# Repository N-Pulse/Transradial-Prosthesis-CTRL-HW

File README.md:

# Transradial Prosthesis Control Board

This work is licensed under a Creative Commons Attribution 4.0 International License

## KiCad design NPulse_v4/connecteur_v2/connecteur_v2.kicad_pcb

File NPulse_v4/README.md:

# Transradial Prosthesis Control Board

This work is licensed under a <a rel="license" href="https://creativecommons.org/licenses/by/4.0/">Creative Commons Attribution 4.0 International License</a>.

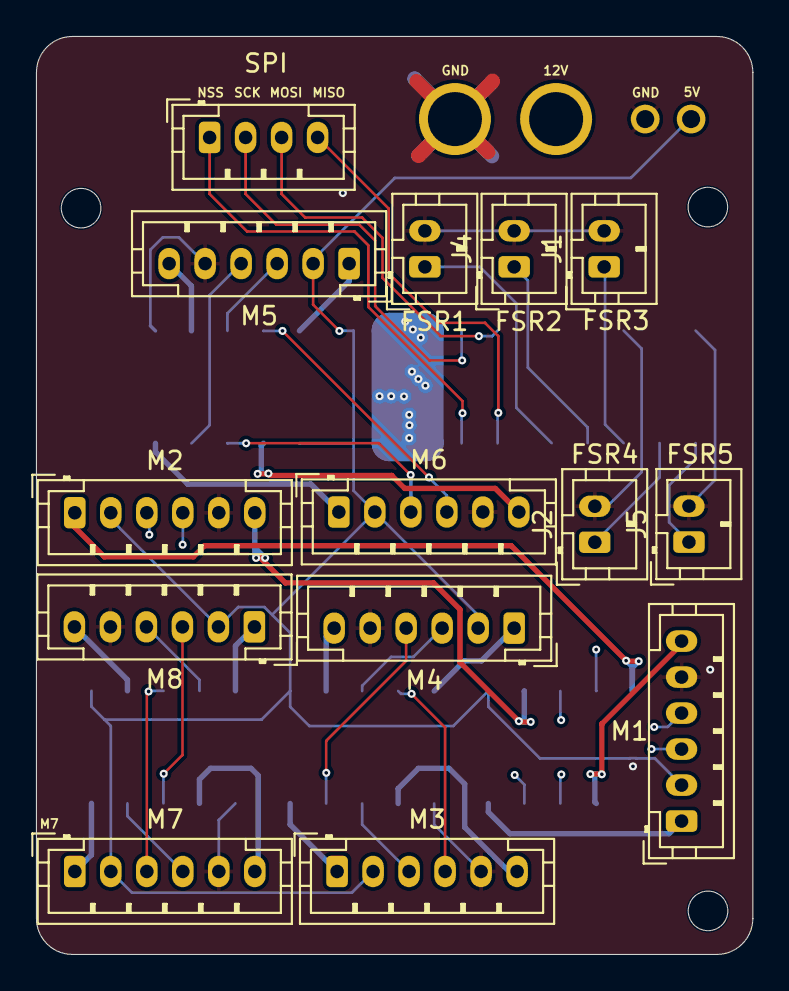
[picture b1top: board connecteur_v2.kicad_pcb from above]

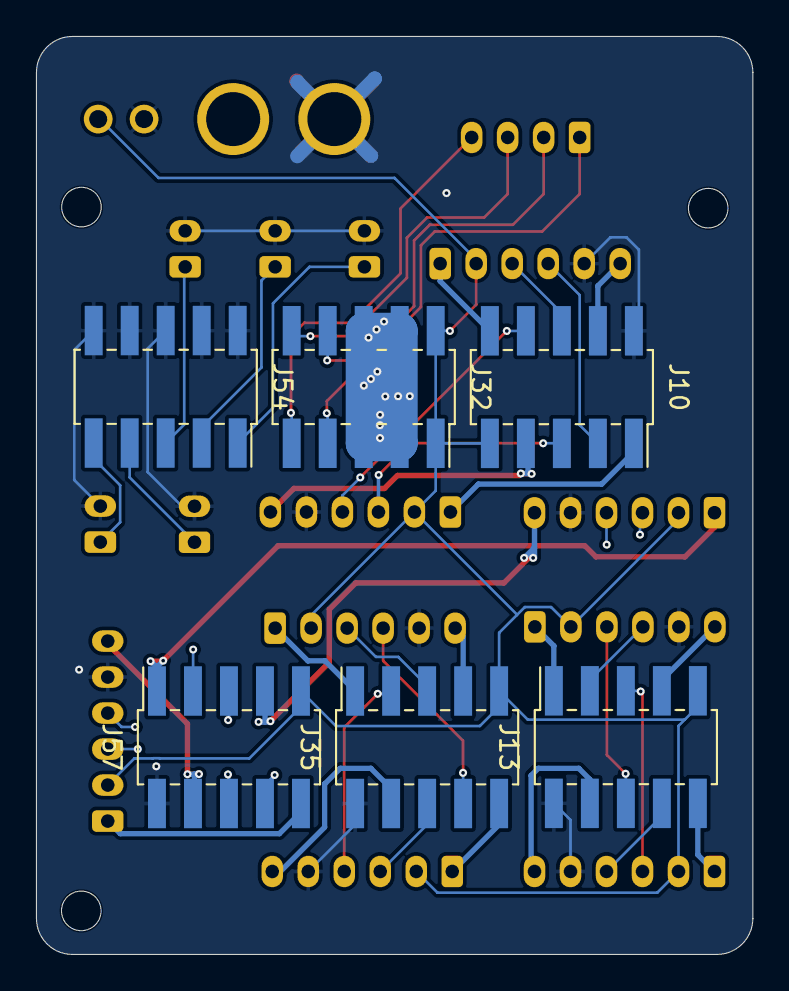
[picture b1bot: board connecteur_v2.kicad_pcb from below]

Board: 4 copper layers, 39.8 x 51.0 mm, 26 parts (6 on the bottom side), 44 nets.

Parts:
H1, H2, H3: MountingHole; MountingHole_2.2mm_M2
J1, J2, J3, J4, J5: Conn_01x02_Socket; JST_PH_B2B-PH-K_1x02_P2.00mm_Vertical
J6: Conn_01x04_Socket; JST_PH_B4B-PH-K_1x04_P2.00mm_Vertical
J10, J13, J32, J35, J54, J57: Conn_02x05_Odd_Even; PinSocket_2x05_P2.00mm_Vertical_SMD
J23, J27, J45: Conn_01x01; SolderWire-0.1sqmm_1x01_D0.4mm_OD1mm
M1, M2, M3, M4, M5, M6, M7, M8: Conn_01x06_Socket; JST_PH_B6B-PH-K_1x06_P2.00mm_Vertical

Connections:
+5V: J10.9, J13.9, J23.1, J32.1, J32.2, J35.9, J57.9, M1.2, M2.2, M3.2, M4.2, M5.2, M6.2, M7.2, M8.2
/+12V: J27.1, J32.3, J32.4, J32.5, J32.6
ENC1_S1: J57.5, M1.4
ENC1_S2: J57.6, M1.3
ENC2_S1: J57.8, M2.4
ENC2_S2: J57.3, M2.3
ENC3_S1: J35.3, M3.4
ENC3_S2: J35.6, M3.3
ENC4_S1: J35.8, M4.4
ENC4_S2: J35.5, M4.3
ENC5_S1: J10.3, M5.4
ENC5_S2: J10.6, M5.3
ENC6_S1: J10.8, M6.4
ENC6_S2: J10.5, M6.3
ENC7_S1: J13.8, M7.4
ENC7_S2: J13.5, M7.3
ENC8_S1: J13.3, M8.4
ENC8_S2: J13.6, M8.3
FSR1: J3.1, J54.1
FSR2: J4.1, J54.3
FSR3: J1.1, J54.5
FSR4: J2.1, J54.7
FSR5: J5.1, J54.9
GND: J1.2, J2.2, J3.2, J4.2, J5.2, J10.2, J13.2, J35.2, J45.1, J54.2, J54.4, J54.6, J54.8, J54.10, J57.2, M1.5, M2.5, M3.5, M4.5, M5.5, M6.5, M7.5, M8.5
M1_1: J57.4, M1.6
M1_2: J57.10, M1.1
M2_1: J57.7, M2.6
M2_2: J57.1, M2.1
M3_1: J35.4, M3.6
M3_2: J35.10, M3.1
M4_1: J35.7, M4.6
M4_2: J35.1, M4.1
M5_1: J10.4, M5.6
M5_2: J10.10, M5.1
M6_1: J10.7, M6.6
M6_2: J10.1, M6.1
M7_1: J13.4, M7.6
M7_2: J13.10, M7.1
M8_1: J13.7, M8.6
M8_2: J13.1, M8.1
MISO: J6.4, J32.9
MOSI: J6.3, J32.10
NSS: J6.1, J32.7
SCK: J6.2, J32.8

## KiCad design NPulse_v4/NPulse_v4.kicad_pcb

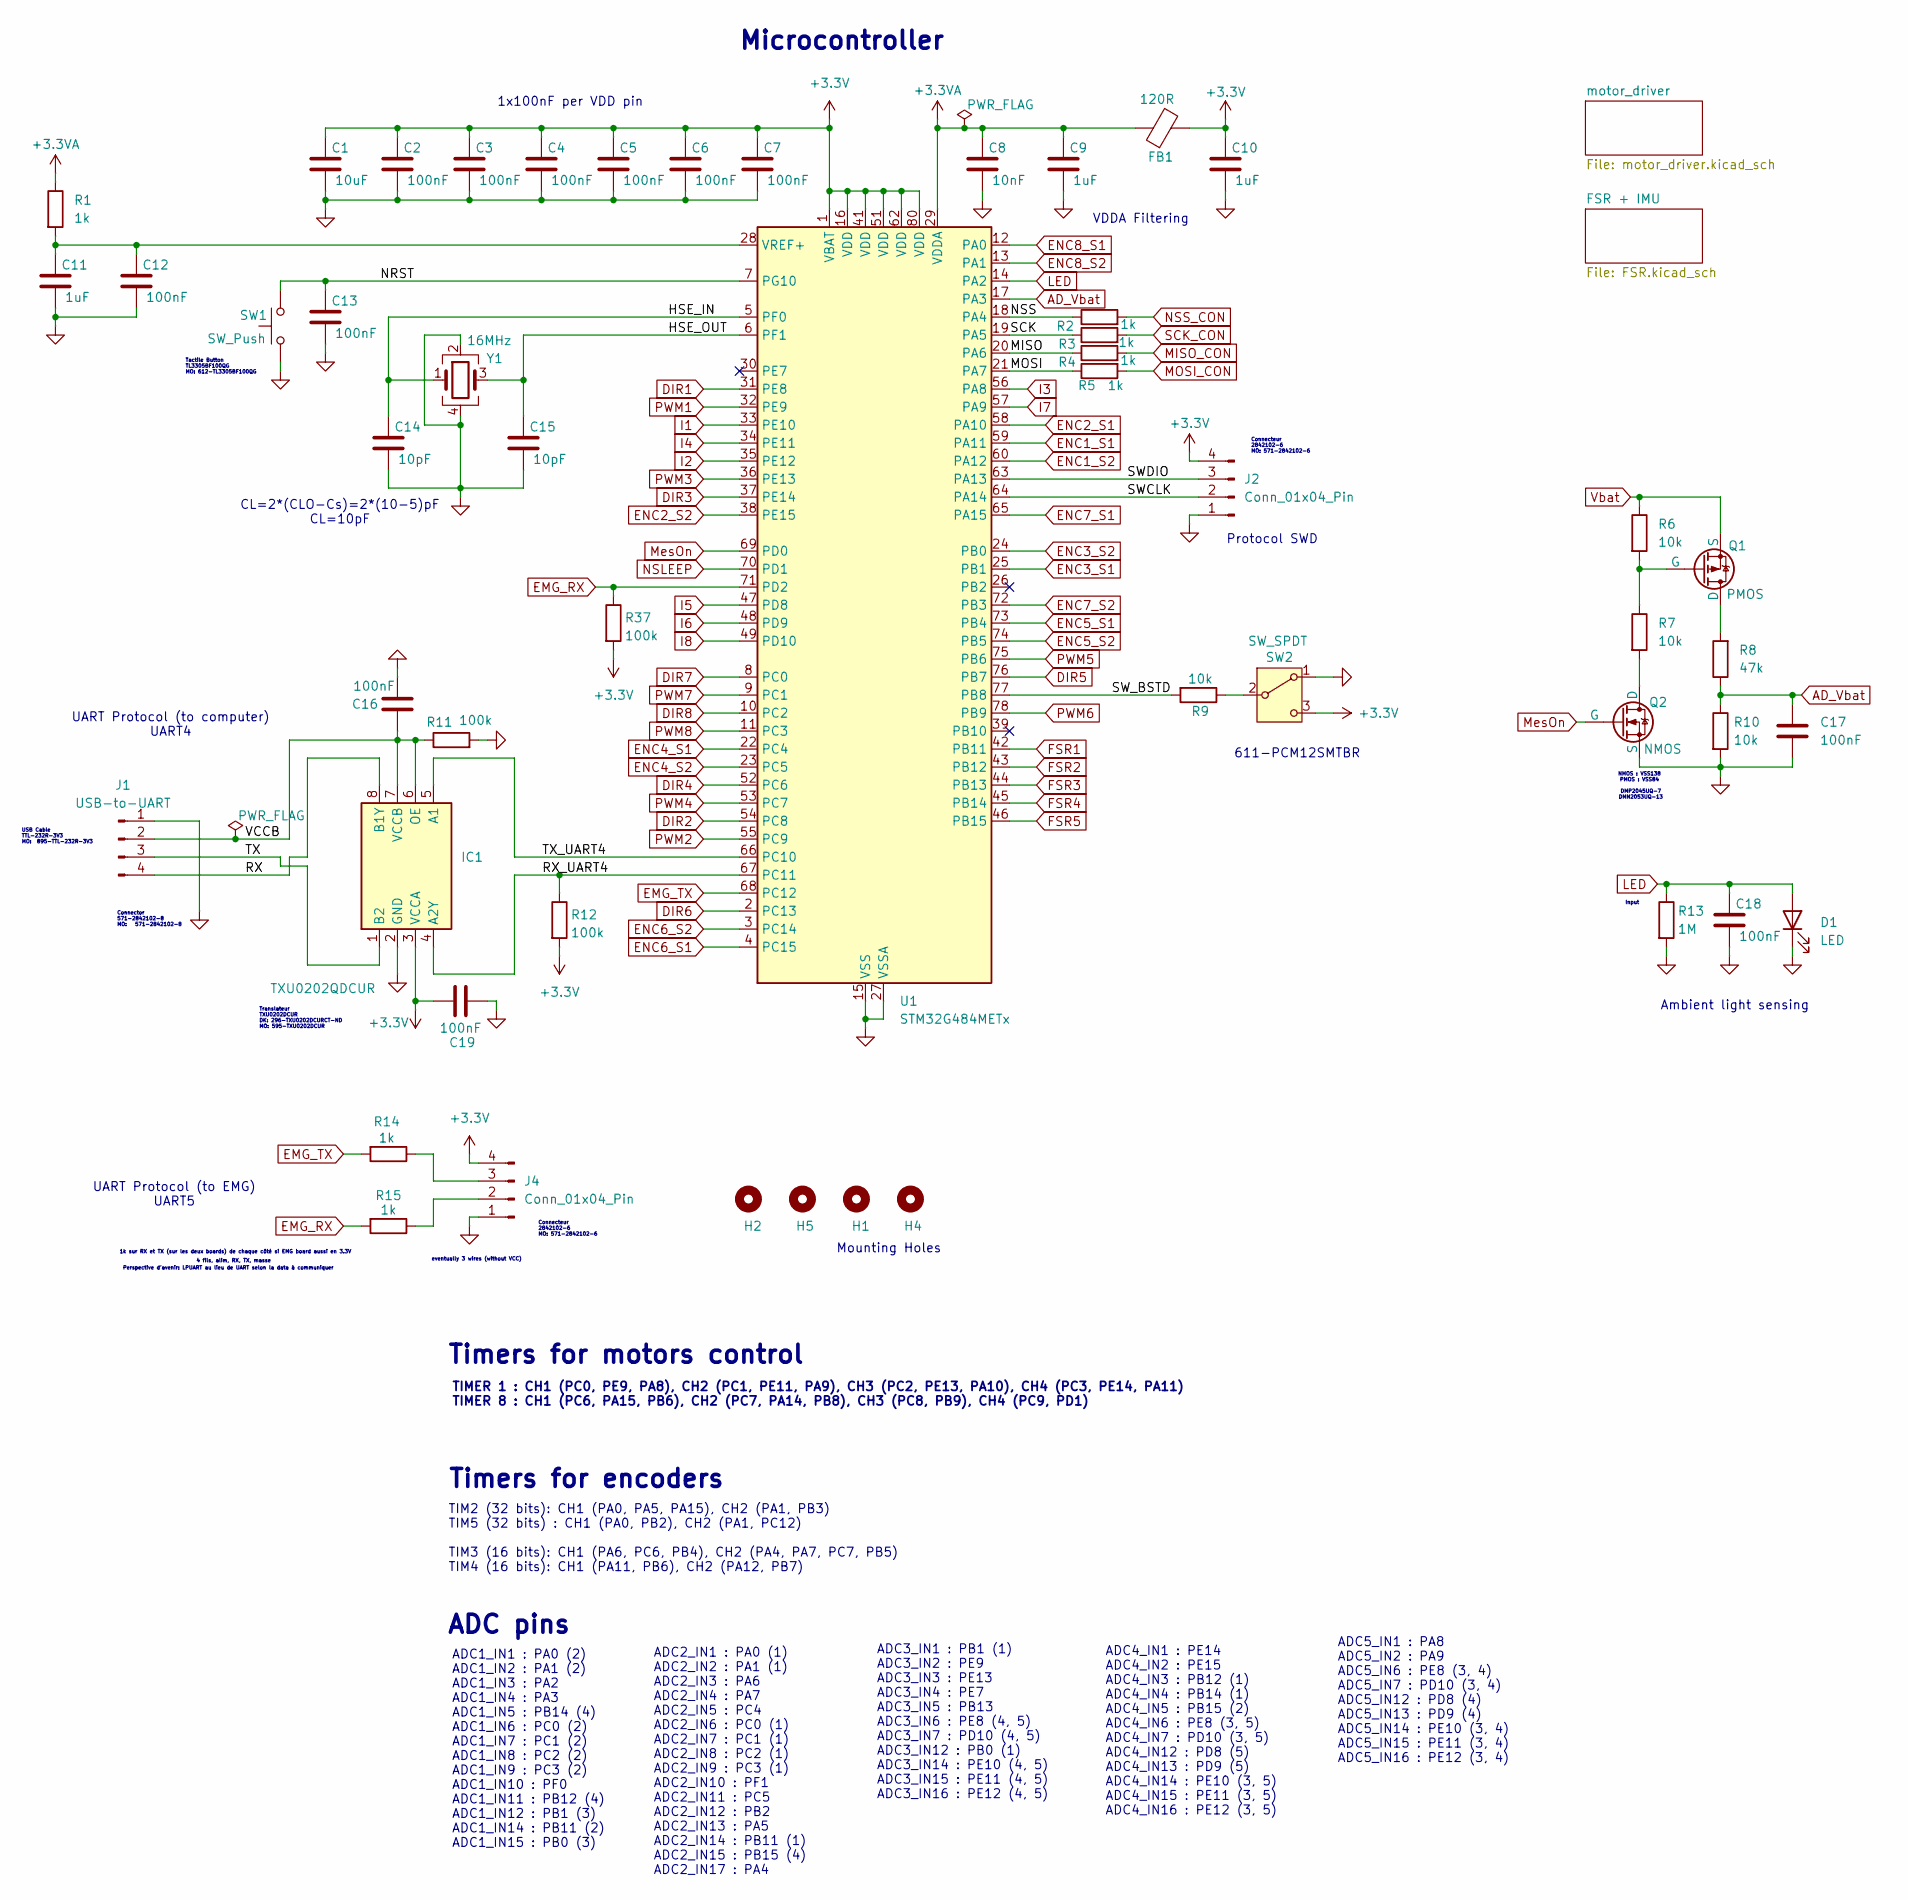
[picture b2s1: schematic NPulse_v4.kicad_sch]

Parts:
C1: 10uF; C_0805_2012Metric
C2, C3, C4, C5, C6, C7, C12, C13, C16, C17, C18, C19: 100nF; C_0402_1005Metric
C8: 10nF; C_0402_1005Metric
C9, C10, C11: 1uF; C_0402_1005Metric
C14, C15: 10pF; C_0402_1005Metric
D1: LED; SOD6439X180N
FB1: 120R; L_0402_1005Metric
H1, H2, H4, H5: MountingHole; MountingHole_2.2mm_M2
IC1: TXU0202QDCUR; SOP50P310X90-8N; Mouser Part Number 595-TXU0202QDCURQ1
J1: USB-to-UART; PinHeader_1x04_P2.54mm_Vertical
J2, J4: Conn_01x04_Pin; PinHeader_1x04_P2.54mm_Vertical
Q1: PMOS; SOT95P240X120-3N
Q2: NMOS; SOT95P240X120-3N
R1, R2, R3, R4, R5, R14, R15: 1k; R_0402_1005Metric
R6, R7, R9, R10: 10k; R_0402_1005Metric
R8: 47k; R_0402_1005Metric
R11, R12, R37: 100k; R_0402_1005Metric
R13: 1M; R_0805_2012Metric
SW1: SW_Push; SW_SPST_TL3305B
SW2: SW_SPDT; SW_SPDT_PCM12
U1: STM32G484METx; LQFP-80_12x12mm_P0.5mm
Y1: 16MHz; Crystal_SMD_3225-4Pin_3.2x2.5mm

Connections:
+3.3V: C1.1, C2.1, C3.1, C4.1, C5.1, C6.1, C7.1, C10.1, C19.2, FB1.2, IC1.3 (VCCA), J2.4, J4.4, R12.2, R37.2, SW2.3 (C), U1.1 (VBAT), U1.16 (VDD), U1.41 (VDD), U1.51 (VDD), U1.62 (VDD), U1.80 (VDD); also elsewhere on the board
+3.3VA: C8.1, C9.1, FB1.1, R1.1, U1.29 (VDDA)
/HSE_IN: C14.1, U1.5 (PF0), Y1.1
/HSE_OUT: C15.1, U1.6 (PF1), Y1.3
/MISO: R4.1, U1.20 (PA6)
/MOSI: R5.1, U1.21 (PA7)
/NRST: C13.1, SW1.1, U1.7 (PG10)
/NSS: R2.1, U1.18 (PA4)
/RX: IC1.8 (B1Y), J1.4
/RX_UART4: IC1.4 (A2Y), R12.1, U1.67 (PC11)
/SCK: R3.1, U1.19 (PA5)
/SWCLK: J2.2, U1.64 (PA14)
/SWDIO: J2.3, U1.63 (PA13)
/SW_BSTD: R9.2, U1.77 (PB8)
/TX: IC1.1 (B2), J1.3
/TX_UART4: IC1.5 (A1), U1.66 (PC10)
/VCCB: C16.2, IC1.6 (OE), IC1.7 (VCCB), J1.2, R11.1
AD_Vbat: C17.1, R8.1, R10.1, U1.17 (PA3)
DIR1: U1.31 (PE8); also elsewhere on the board
DIR2: U1.54 (PC8); also elsewhere on the board
DIR3: U1.37 (PE14); also elsewhere on the board
DIR4: U1.52 (PC6); also elsewhere on the board
DIR5: U1.76 (PB7); also elsewhere on the board
DIR6: U1.2 (PC13); also elsewhere on the board
DIR7: U1.8 (PC0); also elsewhere on the board
DIR8: U1.10 (PC2); also elsewhere on the board
EMG_RX: R15.2, R37.1, U1.71 (PD2)
EMG_TX: R14.2, U1.68 (PC12)
ENC1_S1: U1.59 (PA11); also elsewhere on the board
ENC1_S2: U1.60 (PA12); also elsewhere on the board
ENC2_S1: U1.58 (PA10); also elsewhere on the board
ENC2_S2: U1.38 (PE15); also elsewhere on the board
ENC3_S1: U1.25 (PB1); also elsewhere on the board
ENC3_S2: U1.24 (PB0); also elsewhere on the board
ENC4_S1: U1.22 (PC4); also elsewhere on the board
ENC4_S2: U1.23 (PC5); also elsewhere on the board
ENC5_S1: U1.73 (PB4); also elsewhere on the board
ENC5_S2: U1.74 (PB5); also elsewhere on the board
ENC6_S1: U1.4 (PC15); also elsewhere on the board
ENC6_S2: U1.3 (PC14); also elsewhere on the board
ENC7_S1: U1.65 (PA15); also elsewhere on the board
ENC7_S2: U1.72 (PB3); also elsewhere on the board
ENC8_S1: U1.12 (PA0); also elsewhere on the board
ENC8_S2: U1.13 (PA1); also elsewhere on the board
FSR1: U1.42 (PB11); also elsewhere on the board
FSR2: U1.43 (PB12); also elsewhere on the board
FSR3: U1.44 (PB13); also elsewhere on the board
FSR4: U1.45 (PB14); also elsewhere on the board
FSR5: U1.46 (PB15); also elsewhere on the board
GND: C1.2, C2.2, C3.2, C4.2, C5.2, C6.2, C7.2, C8.2, C9.2, C10.2, C11.2, C12.2, C13.2, C14.2, C15.2, C16.1, C17.2, C18.2, C19.1, D1.1 (K), IC1.2 (GND), J1.1, J2.1, J4.1, Q2.3 (S), R10.2, R11.2, R13.2, SW1.2, SW2.1 (A), U1.15 (VSS), U1.27 (VSSA), U1.40 (VSS), U1.50 (VSS), U1.61 (VSS), U1.79 (VSS), Y1.2, Y1.4; also elsewhere on the board
I1: U1.33 (PE10); also elsewhere on the board
I2: U1.35 (PE12); also elsewhere on the board
I3: U1.56 (PA8); also elsewhere on the board
I4: U1.34 (PE11); also elsewhere on the board
I5: U1.47 (PD8); also elsewhere on the board
I6: U1.48 (PD9); also elsewhere on the board
I7: U1.57 (PA9); also elsewhere on the board
I8: U1.49 (PD10); also elsewhere on the board
LED: C18.1, D1.2 (A), R13.1, U1.14 (PA2)
MISO_CON: R4.2; also elsewhere on the board
MOSI_CON: R5.2; also elsewhere on the board
MesOn: Q2.2 (G), U1.69 (PD0)
NSLEEP: U1.70 (PD1); also elsewhere on the board
NSS_CON: R2.2; also elsewhere on the board
unnamed: J4.2, R15.1
unnamed: J4.3, R14.1
unnamed: Q1.1 (D), R8.2
unnamed: Q1.2 (G), R6.2, R7.1
unnamed: Q2.1 (D), R7.2
unnamed: R9.1, SW2.2 (B)
unnamed: C11.1, C12.1, R1.2, U1.28 (VREF+)
PWM1: U1.32 (PE9); also elsewhere on the board
PWM2: U1.55 (PC9); also elsewhere on the board
PWM3: U1.36 (PE13); also elsewhere on the board
PWM4: U1.53 (PC7); also elsewhere on the board
PWM5: U1.75 (PB6); also elsewhere on the board
PWM6: U1.78 (PB9); also elsewhere on the board
PWM7: U1.9 (PC1); also elsewhere on the board
PWM8: U1.11 (PC3); also elsewhere on the board
SCK_CON: R3.2; also elsewhere on the board
Vbat: Q1.3 (S), R6.1

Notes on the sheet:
1x100nF per VDD pin
NMOS : VSS138 PMOS : VSS84 DMP2045UQ-7 DMN2053UQ-13
1k sur RX et TX (sur les deux boards) de chaque côté si EMG board aussi en 3.3V
UART Protocol (to computer) UART4
ADC3_IN1 : PB1 (1) ADC3_IN2 : PE9 ADC3_IN3 : PE13 ADC3_IN4 : PE7 ADC3_IN5 : PB13 ADC3_IN6 : PE8 (4, 5) ADC3_IN7 : PD10 (4, 5) ADC3_IN12 : PB0 (1) ADC3_IN14 : PE10 (4, 5) ADC3_IN15 : PE11 (4, 5) ADC3_IN16 : PE12 (4, 5)
Mounting Holes
ADC2_IN1 : PA0 (1) ADC2_IN2 : PA1 (1) ADC2_IN3 : PA6 ADC2_IN4 : PA7 ADC2_IN5 : PC4 ADC2_IN6 : PC0 (1) ADC2_IN7 : PC1 (1) ADC2_IN8 : PC2 (1) ADC2_IN9 : PC3 (1) ADC2_IN10 : PF1 ADC2_IN11 : PC5 ADC2_IN12 : PB2 ADC2_IN13 : PA5 ADC2_IN14 : PB11 (1) ADC2_IN15 : PB15 (4) ADC2_IN17 : PA4
USB Cable TTL-232R-3V3 MO: 895-TTL-232R-3V3
Timers for motors control
ADC4_IN1 : PE14 ADC4_IN2 : PE15 ADC4_IN3 : PB12 (1) ADC4_IN4 : PB14 (1) ADC4_IN5 : PB15 (2) ADC4_IN6 : PE8 (3, 5) ADC4_IN7 : PD10 (3, 5) ADC4_IN12 : PD8 (5) ADC4_IN13 : PD9 (5) ADC4_IN14 : PE10 (3, 5) ADC4_IN15 : PE11 (3, 5) ADC4_IN16 : PE12 (3, 5)
Translateur TXU0202DCUR DK: 296-TXU0202DCURCT-ND MO: 595-TXU0202DCUR
TIM2 (32 bits): CH1 (PA0, PA5, PA15), CH2 (PA1, PB3) TIM5 (32 bits) : CH1 (PA0, PB2), CH2 (PA1, PC12) TIM3 (16 bits): CH1 (PA6, PC6, PB4), CH2 (PA4, PA7, PC7, PB5) TIM4 (16 bits): CH1 (PA11, PB6), CH2 (PA12, PB7)
VDDA Filtering
ADC1_IN1 : PA0 (2) ADC1_IN2 : PA1 (2) ADC1_IN3 : PA2 ADC1_IN4 : PA3 ADC1_IN5 : PB14 (4) ADC1_IN6 : PC0 (2) ADC1_IN7 : PC1 (2) ADC1_IN8 : PC2 (2) ADC1_IN9 : PC3 (2) ADC1_IN10 : PF0 ADC1_IN11 : PB12 (4) ADC1_IN12 : PB1 (3) ADC1_IN14 : PB11 (2) ADC1_IN15 : PB0 (3)
Connecteur 2842102-6 MO: 571-2842102-6
eventually 3 wires (without VCC)
TIMER 1 : CH1 (PC0, PE9, PA8), CH2 (PC1, PE11, PA9), CH3 (PC2, PE13, PA10), CH4 (PC3, PE14, PA11) TIMER 8 : CH1 (PC6, PA15, PB6), CH2 (PC7, PA14, PB8), CH3 (PC8, PB9), CH4 (PC9, PD1)
Microcontroller
ADC5_IN1 : PA8 ADC5_IN2 : PA9 ADC5_IN6 : PE8 (3, 4) ADC5_IN7 : PD10 (3, 4) ADC5_IN12 : PD8 (4) ADC5_IN13 : PD9 (4) ADC5_IN14 : PE10 (3, 4) ADC5_IN15 : PE11 (3, 4) ADC5_IN16 : PE12 (3, 4)
CL=2*(CLO-Cs)=2*(10-5)pF CL=10pF
Tactile Button TL3305BF100QG MO: 612-TL3305BF100QG
Perspective d'avenir: LPUART au lieu de UART selon la data à communiquer
Connecteur 2842102-6 MO: 571-2842102-6
4 fils, alim, RX, TX, masse
ADC pins
UART Protocol (to EMG) UART5
Input
Timers for encoders
Ambient light sensing
611-PCM12SMTBR
Connector 571-2842102-8 MO: 571-2842102-8
Protocol SWD

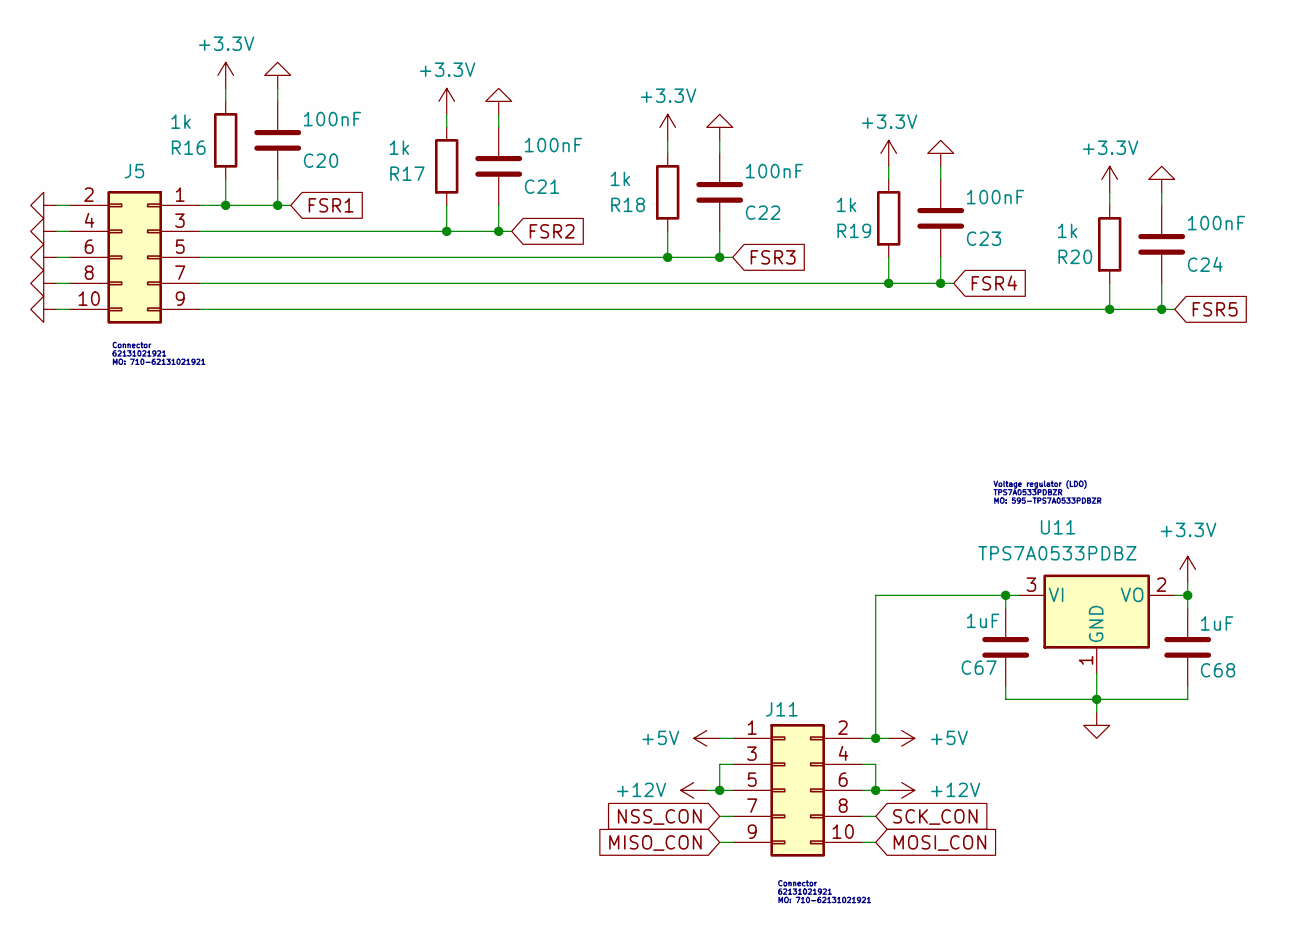
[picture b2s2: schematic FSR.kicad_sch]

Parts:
C20, C21, C22, C23, C24: 100nF; C_0402_1005Metric
C67, C68: 1uF; C_0402_1005Metric
J5, J11: Conn_02x05_Odd_Even; PinHeader_2x05_P2.00mm_Vertical_SMD
R16, R17, R18, R19, R20: 1k; R_0402_1005Metric
U11: TPS7A0533PDBZ; SOT-23

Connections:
+3.3V: C68.2, R16.1, R17.1, R18.1, R19.1, R20.1, U11.2 (VO); also elsewhere on the board
+5V: C67.2, J11.1, J11.2, U11.3 (VI); also elsewhere on the board
+12V: J11.3, J11.4, J11.5, J11.6; also elsewhere on the board
FSR1: C20.2, J5.1, R16.2; also elsewhere on the board
FSR2: C21.2, J5.3, R17.2; also elsewhere on the board
FSR3: C22.2, J5.5, R18.2; also elsewhere on the board
FSR4: C23.2, J5.7, R19.2; also elsewhere on the board
FSR5: C24.2, J5.9, R20.2; also elsewhere on the board
GND: C20.1, C21.1, C22.1, C23.1, C24.1, C67.1, C68.1, J5.2, J5.4, J5.6, J5.8, J5.10, U11.1 (GND); also elsewhere on the board
MISO_CON: J11.9; also elsewhere on the board
MOSI_CON: J11.10; also elsewhere on the board
NSS_CON: J11.7; also elsewhere on the board
SCK_CON: J11.8; also elsewhere on the board

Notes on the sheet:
Connector 62131021921 MO: 710-62131021921
Voltage regulator (LDO) TPS7A0533PDBZR MO: 595-TPS7A0533PDBZR

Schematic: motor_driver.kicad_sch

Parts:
C25, C27, C31, C32, C35, C36, C37, C39, C43, C44, C47, C48, C49, C51, C59, C60, C61, C63, C71, C72: 100nF; C_0402_1005Metric
C26, C28, C29, C30, C33, C34, C38, C40, C41, C42, C45, C46, C50, C52, C53, C54, C57, C58, C62, C64, C65, C66, C69, C70: 10uF; C_0805_2012Metric
IC2, IC3, IC4, IC5, IC6, IC7, IC8, IC9: DRV8220DSGR; WSON8_DSG_TEX; Mouser Part Number 595-DRV8220DSGR
J6, J7, J8, J9: Conn_02x05_Odd_Even; PinHeader_2x05_P2.00mm_Vertical_SMD
L1, L2, L3, L4, L5, L6, L7, L8, L9, L10, L11, L12, L13, L14, L15, L16: 10uH; L_1008_2520Metric
R21, R22, R25, R26, R29, R30, R33, R34: 1k; R_0402_1005Metric
R23, R24, R27, R28, R31, R32, R35, R36: 1; R_0612_1632Metric
U2, U3, U4, U5, U6, U7, U8, U9: SN74LVC002; DHVQFN-14-1EP_2.5x3mm_P0.5mm_EP1x1.5mm

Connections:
+3.3V: C31.1, C32.1, C43.1, C44.1, U2.14 (VCC), U3.14 (VCC), U4.14 (VCC), U5.14 (VCC), U6.14 (VCC), U7.14 (VCC), U8.14 (VCC), U9.14 (VCC); also elsewhere on the board
+5V: J6.9, J7.9, J8.9, J9.9; also elsewhere on the board
+12V: C25.2, C26.1, C27.2, C28.1, C37.2, C38.1, C39.2, C40.1, C49.2, C50.1, C51.2, C52.1, C61.2, C62.1, C63.2, C64.1, IC2.1 (VM), IC3.1 (VM), IC4.1 (VM), IC5.1 (VM), IC6.1 (VM), IC7.1 (VM), IC8.1 (VM), IC9.1 (VM); also elsewhere on the board
DIR1: U2.5, U2.6, U2.12; also elsewhere on the board
DIR2: U4.5, U4.6, U4.12; also elsewhere on the board
DIR3: U6.5, U6.6, U6.12; also elsewhere on the board
DIR4: U8.5, U8.6, U8.12; also elsewhere on the board
DIR5: U3.5, U3.6, U3.12; also elsewhere on the board
DIR6: U5.5, U5.6, U5.12; also elsewhere on the board
DIR7: U7.5, U7.6, U7.12; also elsewhere on the board
DIR8: U9.5, U9.6, U9.12; also elsewhere on the board
ENC1_S1: J9.5; also elsewhere on the board
ENC1_S2: J9.6; also elsewhere on the board
ENC2_S1: J9.8; also elsewhere on the board
ENC2_S2: J9.3; also elsewhere on the board
ENC3_S1: J7.3; also elsewhere on the board
ENC3_S2: J7.6; also elsewhere on the board
ENC4_S1: J7.8; also elsewhere on the board
ENC4_S2: J7.5; also elsewhere on the board
ENC5_S1: J8.3; also elsewhere on the board
ENC5_S2: J8.6; also elsewhere on the board
ENC6_S1: J8.8; also elsewhere on the board
ENC6_S2: J8.5; also elsewhere on the board
ENC7_S1: J6.8; also elsewhere on the board
ENC7_S2: J6.5; also elsewhere on the board
ENC8_S1: J6.3; also elsewhere on the board
ENC8_S2: J6.6; also elsewhere on the board
GND: C31.2, C32.2, C35.2, C36.2, C43.2, C44.2, C47.2, C48.2, C59.2, C60.2, C71.2, C72.2, J6.2, J7.2, J8.2, J9.2, R23.2, R24.2, R27.2, R28.2, R31.2, R32.2, R35.2, R36.2, U2.7 (GND), U3.7 (GND), U4.7 (GND), U5.7 (GND), U6.7 (GND), U7.7 (GND), U8.7 (GND), U9.7 (GND); also elsewhere on the board
I1: C35.1, R21.1; also elsewhere on the board
I2: C47.1, R25.1; also elsewhere on the board
I3: C59.1, R29.1; also elsewhere on the board
I4: C71.1, R33.1; also elsewhere on the board
I5: C36.1, R22.1; also elsewhere on the board
I6: C48.1, R26.1; also elsewhere on the board
I7: C60.1, R30.1; also elsewhere on the board
I8: C72.1, R34.1; also elsewhere on the board
M1_1: C29.1, J9.4, L1.2
M1_2: C33.1, J9.10, L3.2
M2_1: C41.1, J9.7, L5.2
M2_2: C45.1, J9.1, L7.2
M3_1: C53.1, J7.4, L9.2
M3_2: C57.1, J7.10, L11.2
M4_1: C65.1, J7.7, L13.2
M4_2: C69.1, J7.1, L15.2
M5_1: C30.1, J8.4, L2.2
M5_2: C34.1, J8.10, L4.2
M6_1: C42.1, J8.7, L6.2
M6_2: C46.1, J8.1, L8.2
M7_1: C54.1, J6.4, L10.2
M7_2: C58.1, J6.10, L12.2
M8_1: C66.1, J6.7, L14.2
M8_2: C70.1, J6.1, L16.2
NSLEEP: IC2.8 (NSLEEP), IC3.8 (NSLEEP), IC4.8 (NSLEEP), IC5.8 (NSLEEP), IC6.8 (NSLEEP), IC7.8 (NSLEEP), IC8.8 (NSLEEP), IC9.8 (NSLEEP); also elsewhere on the board
unnamed: IC2.2 (OUT1), L1.1
unnamed: IC2.3 (OUT2), L3.1
unnamed: IC3.2 (OUT1), L2.1
unnamed: IC3.3 (OUT2), L4.1
unnamed: IC4.2 (OUT1), L5.1
unnamed: IC4.3 (OUT2), L7.1
unnamed: IC5.2 (OUT1), L6.1
unnamed: IC5.3 (OUT2), L8.1
unnamed: IC6.2 (OUT1), L9.1
unnamed: IC6.3 (OUT2), L11.1
unnamed: IC7.2 (OUT1), L10.1
unnamed: IC7.3 (OUT2), L12.1
unnamed: IC8.2 (OUT1), L13.1
unnamed: IC8.3 (OUT2), L15.1
unnamed: IC9.2 (OUT1), L14.1
unnamed: IC9.3 (OUT2), L16.1
unnamed: U2.3, U2.4
unnamed: U2.2, U2.10, U2.11
unnamed: U3.3, U3.4
unnamed: U3.2, U3.10, U3.11
unnamed: U4.3, U4.4
unnamed: U4.2, U4.10, U4.11
unnamed: U5.3, U5.4
unnamed: U5.2, U5.10, U5.11
unnamed: U6.3, U6.4
unnamed: U6.2, U6.10, U6.11
unnamed: U7.3, U7.4
unnamed: U7.2, U7.10, U7.11
unnamed: U8.3, U8.4
unnamed: U8.2, U8.10, U8.11
unnamed: U9.3, U9.4
unnamed: U9.2, U9.10, U9.11
OUT1_1: IC2.6 (IN1/PH), U2.13
OUT1_2: IC2.5 (IN2/EN), U2.1
OUT2_1: IC4.6 (IN1/PH), U4.13
OUT2_2: IC4.5 (IN2/EN), U4.1
OUT3_1: IC6.6 (IN1/PH), U6.13
OUT3_2: IC6.5 (IN2/EN), U6.1
OUT4_1: IC8.6 (IN1/PH), U8.13
OUT4_2: IC8.5 (IN2/EN), U8.1
OUT5_1: IC3.6 (IN1/PH), U3.13
OUT5_2: IC3.5 (IN2/EN), U3.1
OUT6_1: IC5.6 (IN1/PH), U5.13
OUT6_2: IC5.5 (IN2/EN), U5.1
OUT7_1: IC7.6 (IN1/PH), U7.13
OUT7_2: IC7.5 (IN2/EN), U7.1
OUT8_1: IC9.6 (IN1/PH), U9.13
OUT8_2: IC9.5 (IN2/EN), U9.1
PWM1: U2.8, U2.9; also elsewhere on the board
PWM2: U4.8, U4.9; also elsewhere on the board
PWM3: U6.8, U6.9; also elsewhere on the board
PWM4: U8.8, U8.9; also elsewhere on the board
PWM5: U3.8, U3.9; also elsewhere on the board
PWM6: U5.8, U5.9; also elsewhere on the board
PWM7: U7.8, U7.9; also elsewhere on the board
PWM8: U9.8, U9.9; also elsewhere on the board
pin4_1: C25.1, C26.2, C29.2, C33.2, IC2.4 (GND), R21.2, R23.1
pin4_2: C37.1, C38.2, C41.2, C45.2, IC4.4 (GND), R25.2, R27.1
pin4_3: C49.1, C50.2, C53.2, C57.2, IC6.4 (GND), R29.2, R31.1
pin4_4: C61.1, C62.2, C65.2, C69.2, IC8.4 (GND), R33.2, R35.1
pin4_5: C27.1, C28.2, C30.2, C34.2, IC3.4 (GND), R22.2, R24.1
pin4_6: C39.1, C40.2, C42.2, C46.2, IC5.4 (GND), R26.2, R28.1
pin4_7: C51.1, C52.2, C54.2, C58.2, IC7.4 (GND), R30.2, R32.1
pin4_8: C63.1, C64.2, C66.2, C70.2, IC9.4 (GND), R34.2, R36.1

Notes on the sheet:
connecter à la pin 4 au lieu de la vraie masse pour éviter les rebouclages de courant
Thermal pad au terminal de la pin 4
Motor driver DRV8220DSGR MO: 595-DRV8220DSGR package: WSON
Shunt LTR18EZPFL1R00 MO: 755-LTR18EZPFL1R00
Capacitor (2 fois) GRM21BC81C106KE5K MO: 81-GRM21BC81C106KE5K
Inductance (2 fois) AOTA-B252010S100MT MO: 815-AOTB252010S100MT
grande par rapport au shunt
Connector 62131021921 MO: 710-62131021921
4 NOR-Gates (2 fois) 595-SN74LVC02ABQAR MO: 595-SN74LVC02ABQAR Package_DFN_QFN:DHVQFN-14-1EP_2.5x3mm_P0.5mm_EP1x1.5mm
Motor VCC Encoder GND Encoder Signal 1 Encoder Signal 2 Encoder VCC Motor GND
C119, C114, C115, C117 à la pin 4 pour éviter les rebouclages de courant

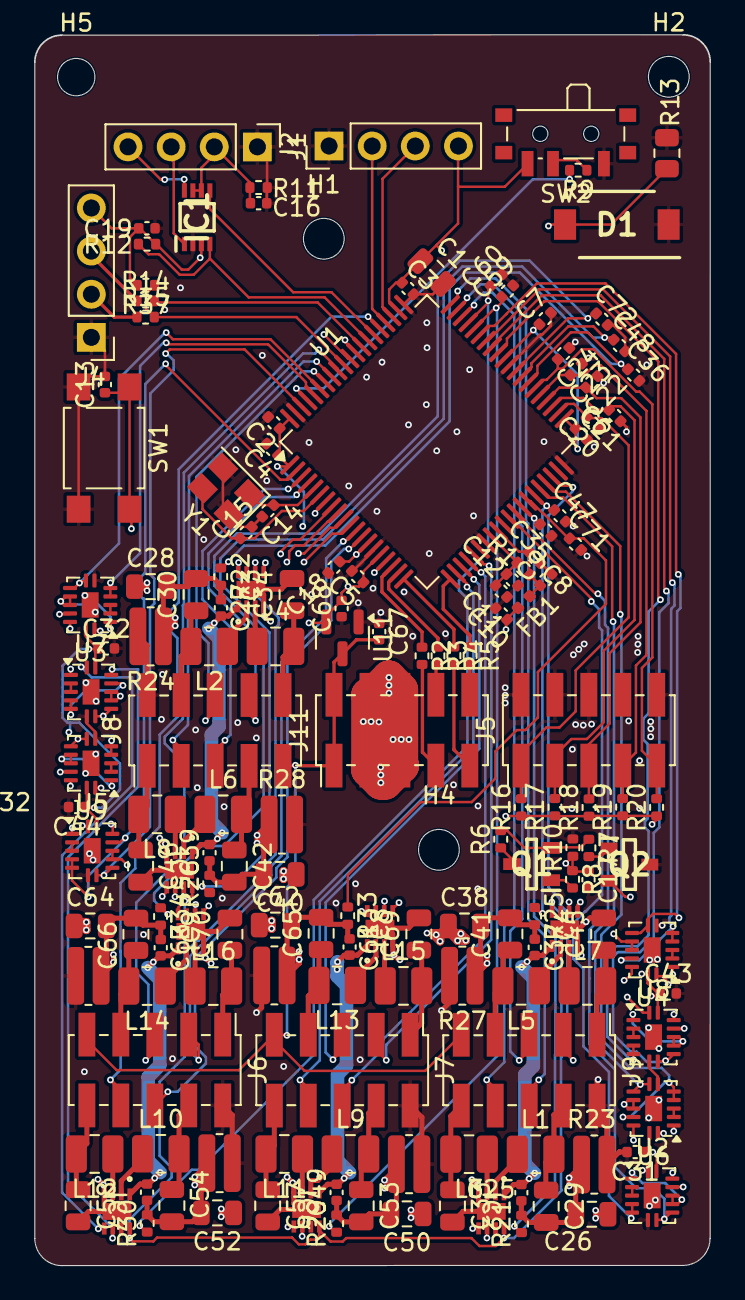
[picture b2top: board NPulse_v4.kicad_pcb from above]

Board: 4 copper layers, 39.8 x 72.5 mm, 162 parts (0 on the bottom side), 155 nets.

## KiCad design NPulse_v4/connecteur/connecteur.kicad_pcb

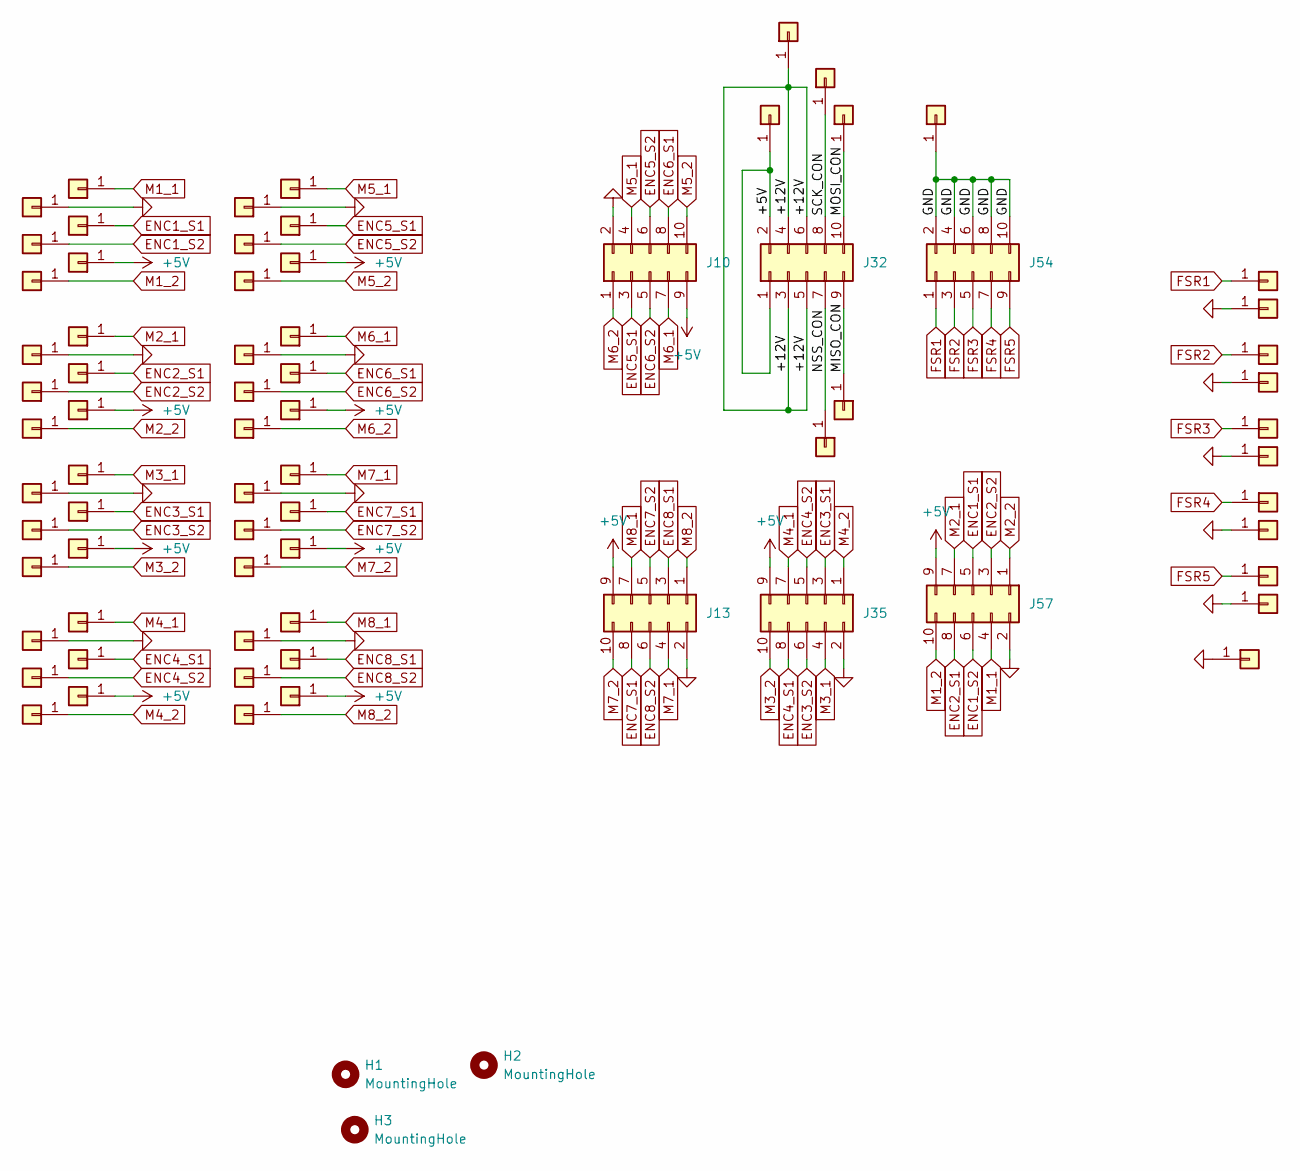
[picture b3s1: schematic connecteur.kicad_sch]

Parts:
H1, H2, H3: MountingHole; MountingHole_2.2mm_M2
J1, J2, J3, J4, J5, J6, J7, J8, J9, J11, J12, J14, J15, J16, J17, J18, J19, J20, J21, J22, J23, J25, J26, J27, J29, J30, J34, J36, J37, J38, J39, J40, J41, J42, J43, J44, J45, J46, J47, J48, J49, J50, J51, J52, J53, J55, J56, J58, J59, J60, J61, J62, J63, J64, J65, J66, J67, J68, J69, J70, J72, J73, J74, J75, J76, J77: Conn_01x01; SolderWire-0.1sqmm_1x01_D0.4mm_OD1mm
J10, J13, J32, J35, J54, J57: Conn_02x05_Odd_Even; PinSocket_2x05_P2.00mm_Vertical_SMD

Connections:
+5V: J6.1, J10.9, J13.9, J14.1, J20.1, J23.1, J30.1, J32.1, J32.2, J35.9, J44.1, J53.1, J57.9, J63.1, J70.1
/+12V: J27.1, J32.3, J32.4, J32.5, J32.6
/MISO_CON: J32.9, J42.1
/MOSI_CON: J32.10, J41.1
/NSS_CON: J32.7, J38.1
/SCK_CON: J32.8, J37.1
ENC1_S1: J4.1, J57.5
ENC1_S2: J3.1, J57.6
ENC2_S1: J12.1, J57.8
ENC2_S2: J8.1, J57.3
ENC3_S1: J19.1, J35.3
ENC3_S2: J16.1, J35.6
ENC4_S1: J29.1, J35.8
ENC4_S2: J22.1, J35.5
ENC5_S1: J10.3, J43.1
ENC5_S2: J10.6, J36.1
ENC6_S1: J10.8, J52.1
ENC6_S2: J10.5, J48.1
ENC7_S1: J13.8, J62.1
ENC7_S2: J13.5, J58.1
ENC8_S1: J13.3, J69.1
ENC8_S2: J13.6, J66.1
FSR1: J54.1, J72.1
FSR2: J46.1, J54.3
FSR3: J54.5, J55.1
FSR4: J54.7, J64.1
FSR5: J54.9, J75.1
GND: J2.1, J7.1, J10.2, J13.2, J15.1, J21.1, J34.1, J35.2, J45.1, J47.1, J50.1, J54.2, J54.4, J54.6, J54.8, J54.10, J56.1, J57.2, J60.1, J65.1, J73.1, J74.1, J76.1, J77.1
M1_1: J1.1, J57.4
M1_2: J5.1, J57.10
M2_1: J11.1, J57.7
M2_2: J9.1, J57.1
M3_1: J18.1, J35.4
M3_2: J17.1, J35.10
M4_1: J26.1, J35.7
M4_2: J25.1, J35.1
M5_1: J10.4, J40.1
M5_2: J10.10, J39.1
M6_1: J10.7, J51.1
M6_2: J10.1, J49.1
M7_1: J13.4, J61.1
M7_2: J13.10, J59.1
M8_1: J13.7, J68.1
M8_2: J13.1, J67.1

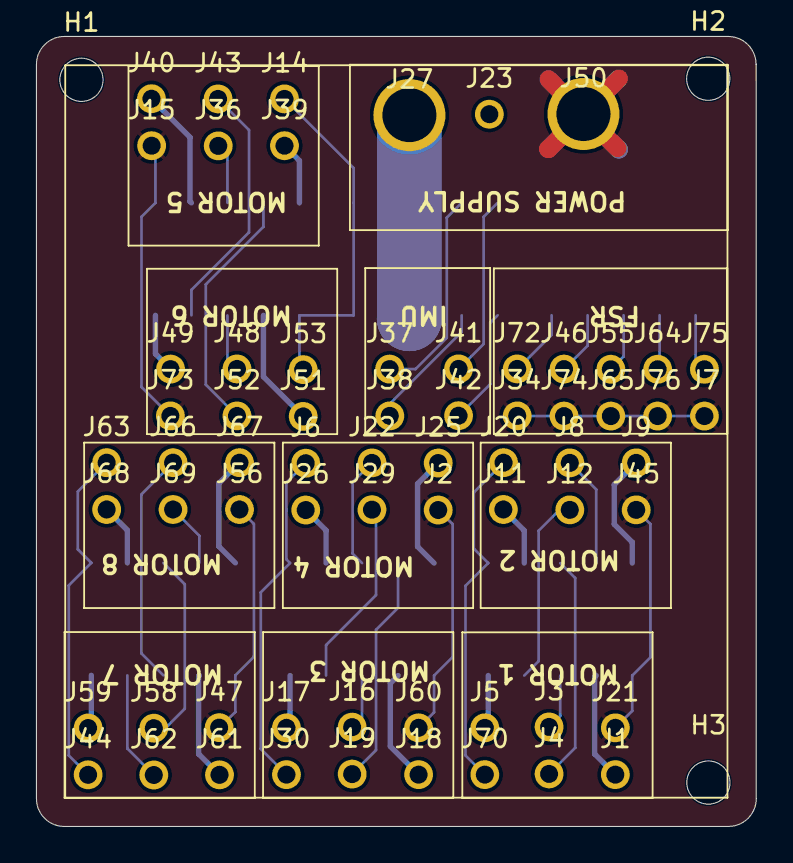
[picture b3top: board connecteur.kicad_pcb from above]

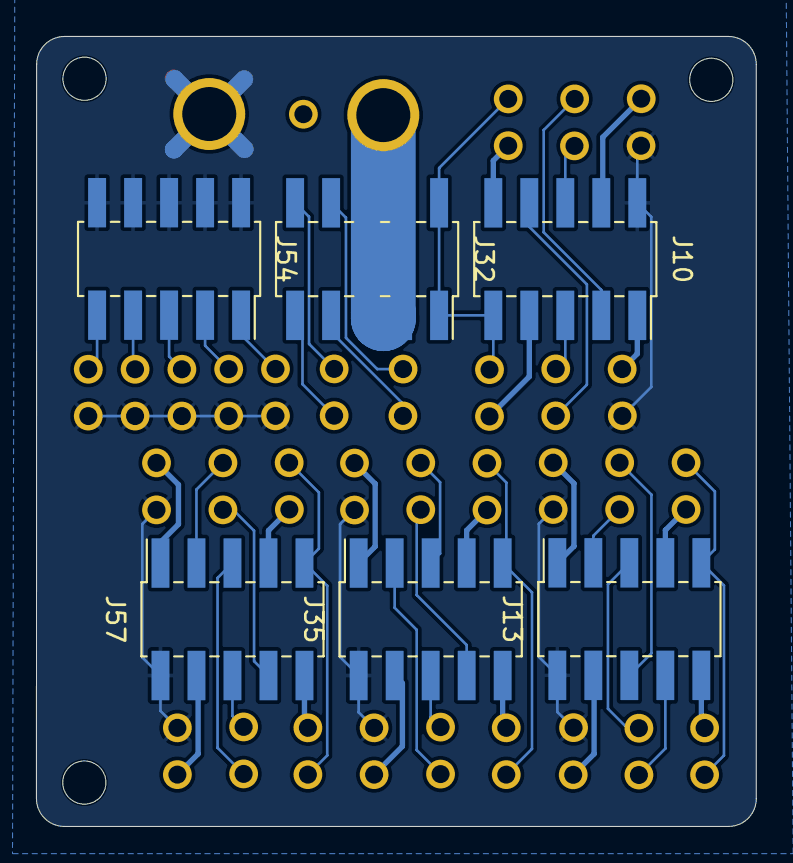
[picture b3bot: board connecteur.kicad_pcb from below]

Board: 4 copper layers, 40.0 x 43.9 mm, 74 parts (6 on the bottom side), 44 nets.

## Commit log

2024-11-22 add my work done so far on git
2024-12-02 Add MCU, FSR, motor drivers, light sensing
2024-12-08 Version 3 - motor driver updated, FSR updated
2024-12-09 Adding FSR datasheet
2025-02-24 Version 4
2025-02-26 some modifications on the routing
2025-02-26 clean the repo a little bit
2025-03-07 Udate mounting holes positions
2025-03-08 remove gnd via from pwm trace and generate gerbers
2025-03-09 Few corrections: tracks, via, thermal pad
2025-03-10 add 5v-gnd pair
2025-03-10 generate gerber files
2025-03-12 add license
2025-03-12 add link to license
2025-04-06 Correct LDO schematic and update connectors to through-hole footprints
2025-04-08 convert pin headers to 2.54mm
2025-05-06 Second version of Hat + add Pull-up on UART_RX of the control Board
2025-05-06 add some via on Hat for emi
2025-05-06 Replace vias and change connectors footprint on control board
2025-05-07 add text on hat board, generate gerbers
2025-05-08 restructure files and change vias on hat to 0.45mm diam
